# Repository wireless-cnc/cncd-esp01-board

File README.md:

# CNCD ESP-01 Board

🔴 **WARNING** - the hardware / firmware of the project is not stable and has a showstopper issue https://github.com/wireless-cnc/cncd-esp01/issues/1

The motherboard for ESP-01 running CNCD firmware.

## How to use it

1. Grab the ESP-01 board and flash it with [CNCD firmware](https://github.com/wireless-cnc/cncd-esp01)
2. Insert ESP-01 into the slot, the arrow on the top side shows the direction of the ESP-01 antenna
3. Connect the board with the CNC Controller Board using [Offline Controller's cable](https://docs.sainsmart.com/article/zinzutpbhg-genmitsu-3018-pro-offline-controller-guide)
4. Power on CNC
5. Configure WiFi connection of CNCD 
6. Install and run [Wireless CNC Controller](https://github.com/wireless-cnc/cnc-controller/releases)
7. Now you can upload CNC job to controller and launch it!

## What's there

This repo contains source files developed in KiCAD 7.0:

* Board schematic
* PCB layout
* Gerber files

## Board features

* IDP connector compatible with CNC-3018 offline controllers
* Onboard 5V to 3.3V voltage regulator for powering ESP chip
* Delayed serial interface initialization
* Voltage level conversion from CNC 5V serial to ESP's 3.3V serial

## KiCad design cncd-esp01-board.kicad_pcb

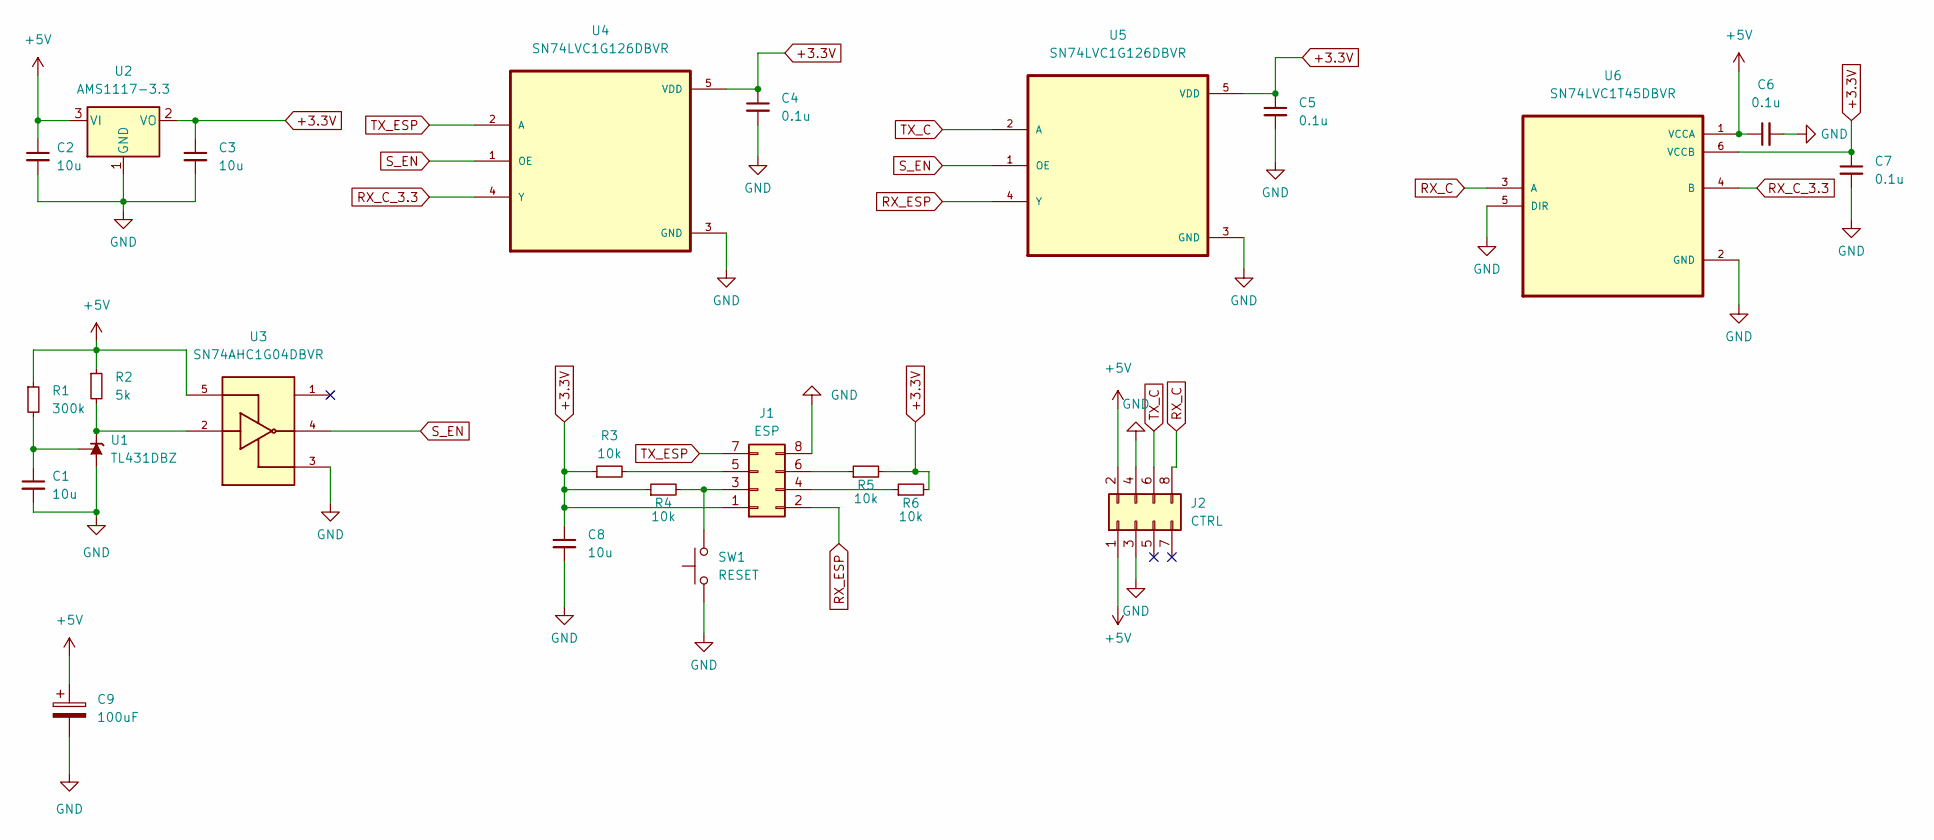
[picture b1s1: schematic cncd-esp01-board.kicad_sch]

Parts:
C1, C2, C3, C8: 10u; C_0805_2012Metric
C4, C5, C6, C7: 0.1u; C_0805_2012Metric
C9: 100uF; CP_EIA-3528-21_Kemet-B
J1: ESP; PinSocket_2x04_P2.54mm_Vertical
J2: CTRL; IDC-Header_2x04_P2.54mm_Horizontal
R1: 300k; R_0805_2012Metric
R2: 5k; R_0805_2012Metric
R3, R4, R5, R6: 10k; R_0805_2012Metric
SW1: RESET; SW_SPST_CK_RS282G05A3
U1: TL431DBZ; SOT-23
U2: AMS1117-3.3; SOT-223-3_TabPin2
U3: SN74AHC1G04DBVR; SOT-23-5; PARTREV AD
U4, U5: SN74LVC1G126DBVR; SOT-23-5
U6: SN74LVC1T45DBVR; SOT-23-6

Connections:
+3.3V: C3.1, C4.1, C5.1, C7.1, C8.1, J1.1, R3.1, R4.1, R5.2, R6.2, U2.2 (VO), U4.5 (VDD), U5.5 (VDD), U6.6 (VCCB)
+5V: C2.1, C6.1, C9.1, J2.1, J2.2, R1.1, R2.1, U2.3 (VI), U3.5, U6.1 (VCCA)
GND: C1.2, C2.2, C3.2, C4.2, C5.2, C6.2, C7.2, C8.2, C9.2, J1.8, J2.3, J2.4, SW1.1, U1.3 (A), U2.1 (GND), U3.3, U4.3 (GND), U5.3 (GND), U6.2 (GND), U6.5 (DIR)
unnamed: J1.3, R4.2, SW1.2
unnamed: J1.4, R6.1
unnamed: J1.5, R3.2
unnamed: J1.6, R5.1
unnamed: R2.2, U1.1 (K), U3.2
unnamed: C1.1, R1.2, U1.2 (REF)
RX_C: J2.8, U6.3 (A)
RX_C_3.3: U4.4 (Y), U6.4 (B)
RX_ESP: J1.2, U5.4 (Y)
S_EN: U3.4, U4.1 (OE), U5.1 (OE)
TX_C: J2.6, U5.2 (A)
TX_ESP: J1.7, U4.2 (A)

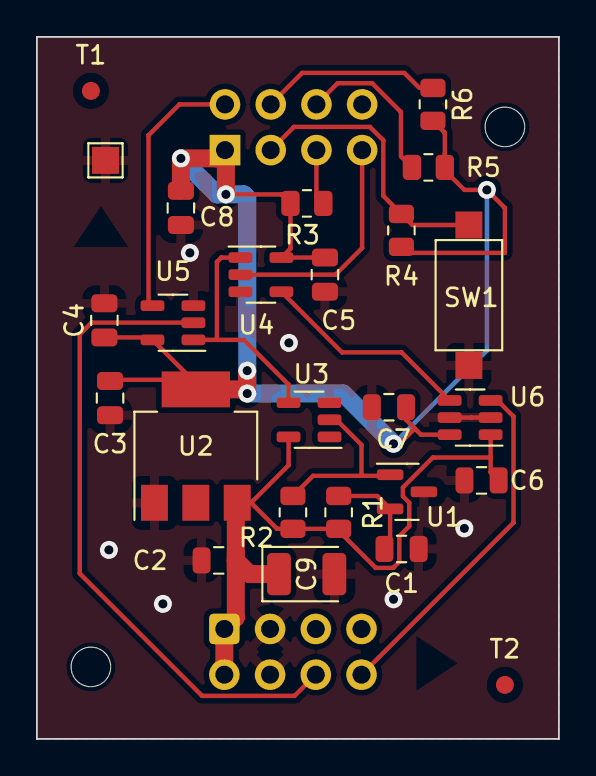
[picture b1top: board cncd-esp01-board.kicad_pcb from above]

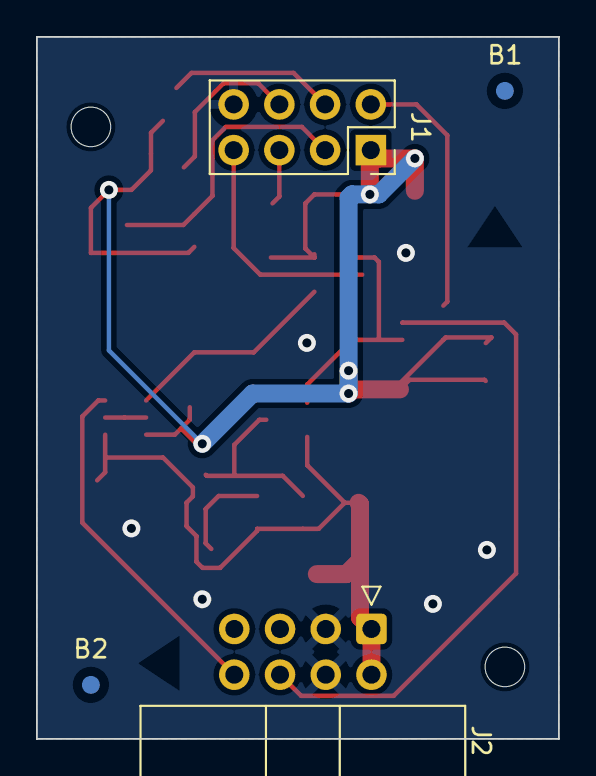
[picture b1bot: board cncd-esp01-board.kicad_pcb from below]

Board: 2 copper layers, 29.0 x 39.0 mm, 28 parts (4 on the bottom side), 15 nets.

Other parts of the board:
B1, B2: Fiducial_1mm_Mask2mm
T1, T2: Fiducial_1mm_Mask2mm

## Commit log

2023-03-21 Update docs
2023-04-05 Add 100uF bypass capacitor to mitigate #1
